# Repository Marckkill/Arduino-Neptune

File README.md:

# Arduino Neptune

> Repositorio do kit Arduino Neptune, um kit didatico para uso em sala de aula. 
> Usado no aprendizado de microcontroladores

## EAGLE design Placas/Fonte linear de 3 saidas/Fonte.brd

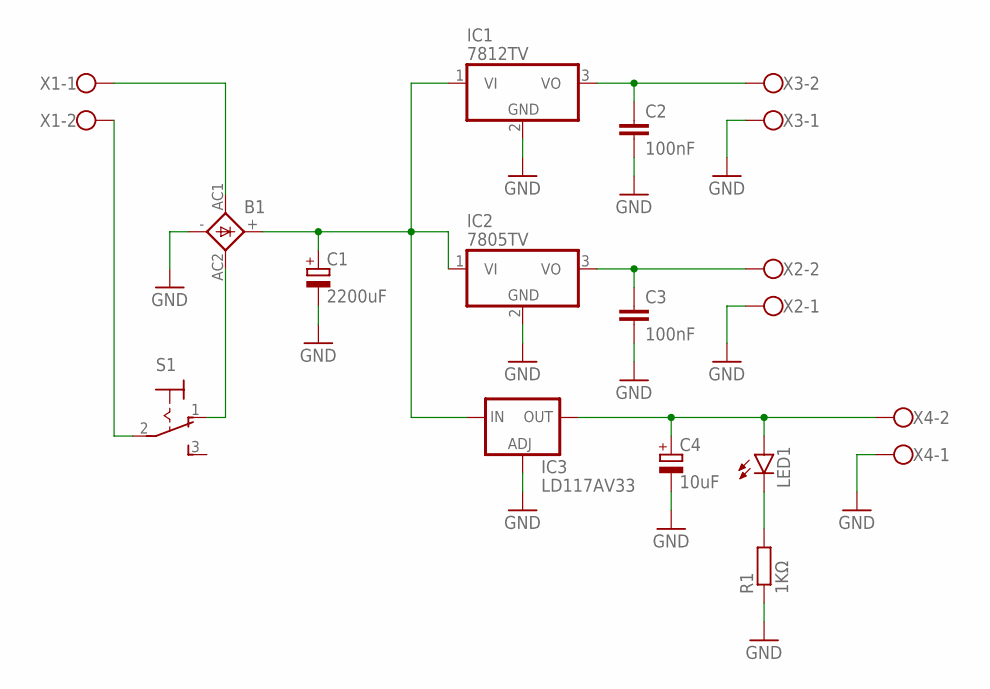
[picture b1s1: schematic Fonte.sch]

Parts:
B1: 2KBB
C1: 2200uF; E5-13
C2, C3: 100nF; C025-024X044
C4: 10uF; E1,8-4
IC1: 7812TV; TO220V
IC2: 7805TV; TO220V
IC3: LD117AV33; TO220S
LED1: LED5MM
R1: 1KΩ; 0207/10
S1: M9040P
X1, X2, X3, X4: W237-102

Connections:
3.3V: C4.+, IC3.2 (OUT), LED1.A, X4.2
5V: C2.1, IC1.3 (VO), X3.2
12V: C3.1, IC2.3 (VO), X2.2
AC1: B1.AC1, X1.1
AC2: S1.2, X1.2
CHAVE: B1.AC2, S1.1 (O)
GND: B1.-, C1.-, C2.2, C3.2, C4.-, IC1.2 (GND), IC2.2 (GND), IC3.1 (ADJ), R1.1, X2.1, X3.1, X4.1
LED: LED1.K (C), R1.2
MAIN: B1.+, C1.+, IC1.1 (VI), IC2.1 (VI), IC3.3 (IN)

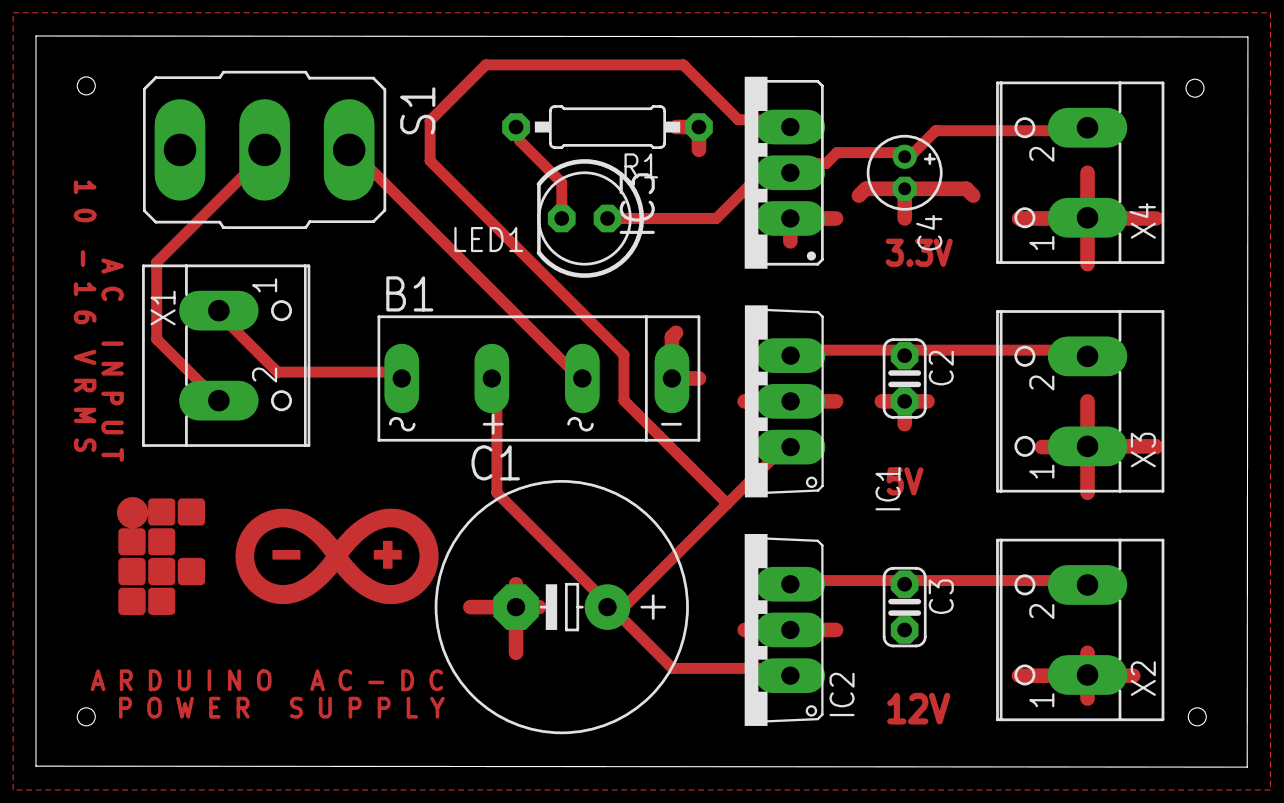
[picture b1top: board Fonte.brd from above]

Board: 2 copper layers, 67.3 x 40.6 mm, 15 parts (0 on the bottom side), 9 nets.

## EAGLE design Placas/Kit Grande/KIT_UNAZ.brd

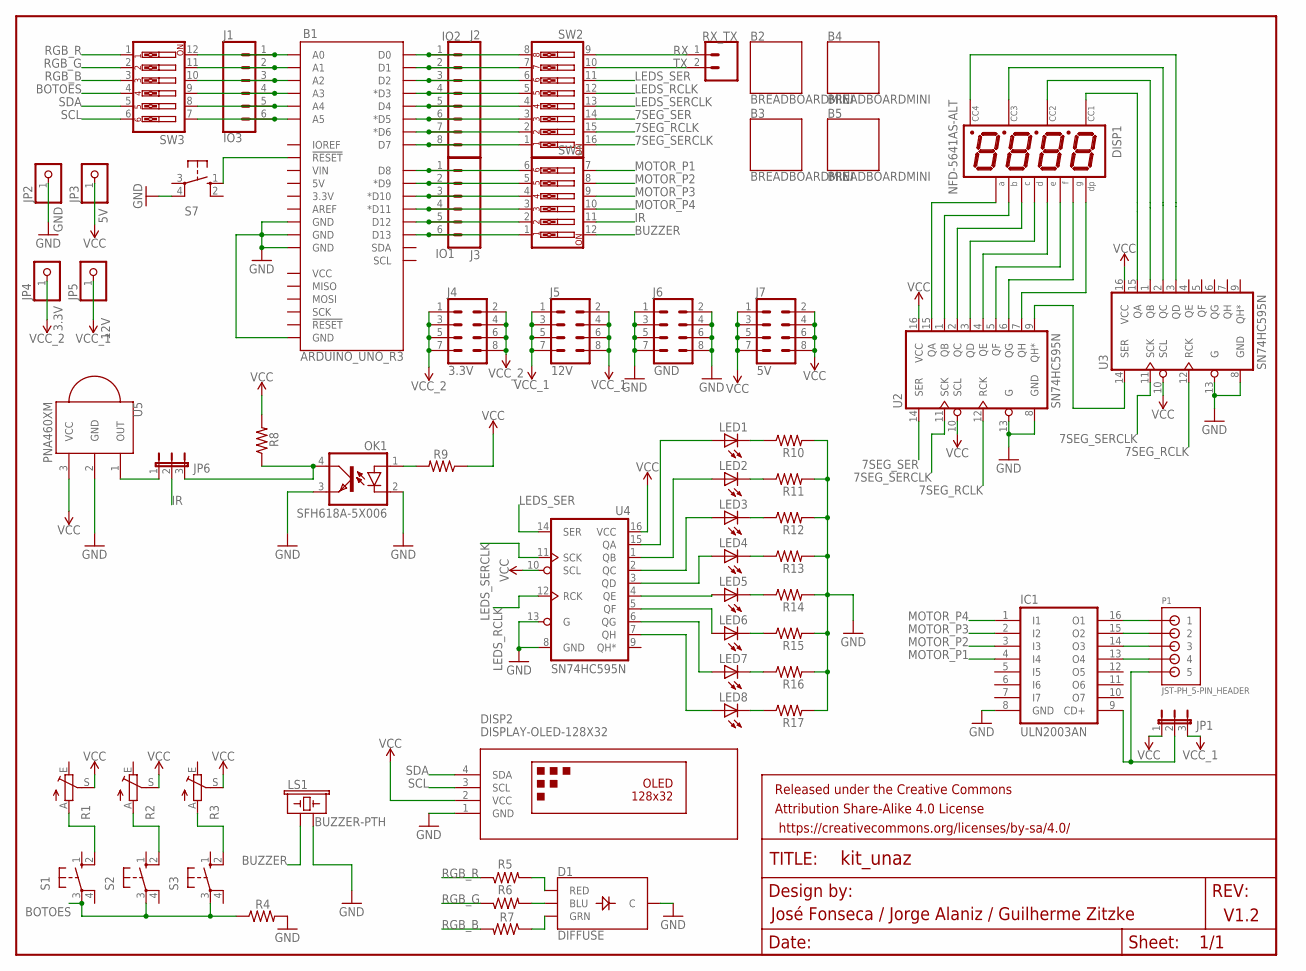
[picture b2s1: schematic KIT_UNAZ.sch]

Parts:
B1: ARDUINO_UNO_R3; ARDUINO_R3
B2, B3, B4, B5: BREADBOARDMINI; BREADBOARD-MINI
D1: DIFFUSE; WS2812B-PTH-KIT
DISP1: NFD-5641AS-ALT; NFD-5641
DISP2: DISPLAY-OLED-128X32
FRAME1: FRAME-LETTER; CREATIVE_COMMONS
IC1: ULN2003AN; DIL16
J1: IO3; 1X06
J2: IO2; 1X08
J3: IO1; 1X06
J4: 3.3V; 2X4
J5: 12V; 2X4
J6: GND; 2X4
J7: 5V; 2X4
JP1, JP6: JP2E; JP2
JP2: GND; 1X01
JP3: 5V; 1X01
JP4: 3.3V; 1X01
JP5: 12V; 1X01
LED1, LED2, LED3, LED4, LED5, LED6, LED7, LED8: LED5MM
LS1: BUZZER-PTH; BUZZER-12MM
OK1: SFH618A-5X006; DIP4-400
P1: JST-PH_5-PIN_HEADER; JST_B5B-PH_HEADER
R1, R2, R3: TRIM_EU-B64Y; B64Y
R4, R5, R6, R7, R8, R9, R10, R11, R12, R13, R14, R15, R16, R17: R-US_0204/7; 0204/7
RX_TX: CONN_02; 1X02
S1, S2, S3, S7: 40-XX; B3F-40XX
SW1, SW3: SW_DIP-6; EDG-06
SW2: SW_DIP-8; EDG-08
U2, U3, U4: SN74HC595N; DIP16
U5: PNA460XM

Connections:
7SEG_RCLK: SW2.15, U2.12 (RCK), U3.12 (RCK)
7SEG_SER: SW2.14, U2.14 (SER)
7SEG_SERCLK: SW2.16, U2.11 (SCK), U3.11 (SCK)
BOTOES: R4.1, S1.3, S2.3, S3.3, SW3.4
BUZZER: LS1.+ (1), SW1.12
GND: B1.GND@1 (GND), B1.GND@2 (GND), B1.GND@3 (GND), B1.GND@4 (GND), D1.2 (C), DISP2.1 (GND), IC1.8 (GND), J6.1, J6.2, J6.3, J6.4, J6.5, J6.6, J6.7, J6.8, JP2.1, LS1.- (2), OK1.2 (C), OK1.3 (EMIT), R4.2, R10.2, R11.2, R12.2, R13.2, R14.2, R15.2, R16.2, R17.2, S7.4 (P1), U2.8 (GND), U2.13 (G), U3.8 (GND), U3.13 (G), U4.8 (GND), U4.13 (G), U5.2 (GND)
IR: JP6.2, SW1.11
LEDS_RCLK: SW2.12, U4.12 (RCK)
LEDS_SER: SW2.11, U4.14 (SER)
LEDS_SERCLK: SW2.13, U4.11 (SCK)
MOTOR_P1: IC1.4 (I4), SW1.7
MOTOR_P2: IC1.3 (I3), SW1.8
MOTOR_P3: IC1.2 (I2), SW1.9
MOTOR_P4: IC1.1 (I1), SW1.10
unnamed: R1.A, S1.2 (S1)
unnamed: R2.A, S2.2 (S1)
unnamed: R3.A, S3.2 (S1)
unnamed: B1.A0, J1.1, SW3.12
unnamed: B1.A1, J1.2, SW3.11
unnamed: B1.A2, J1.3, SW3.10
unnamed: B1.A3, J1.4, SW3.9
unnamed: B1.A4, J1.5, SW3.8
unnamed: B1.A5, J1.6, SW3.7
unnamed: D1.1 (RED), R5.2
unnamed: D1.4 (BLU), R6.2
unnamed: D1.3 (GRN), R7.1
unnamed: DISP1.P$11, U2.15 (QA)
unnamed: B1.D13, J3.6, SW1.1
unnamed: B1.D12, J3.5, SW1.2
unnamed: LED5.K (C), R14.1
unnamed: LED4.K (C), R13.1
unnamed: LED1.K (C), R10.1
unnamed: LED2.K (C), R11.1
unnamed: LED3.K (C), R12.1
unnamed: LED6.K (C), R15.1
unnamed: LED1.A, U4.15 (QA)
unnamed: LED2.A, U4.1 (QB)
unnamed: LED3.A, U4.2 (QC)
unnamed: LED4.A, U4.3 (QD)
unnamed: LED5.A, U4.4 (QE)
unnamed: LED6.A, U4.5 (QF)
unnamed: DISP1.P$7, U2.1 (QB)
unnamed: DISP1.P$4, U2.2 (QC)
unnamed: DISP1.P$2, U2.3 (QD)
unnamed: DISP1.P$1, U2.4 (QE)
unnamed: DISP1.P$10, U2.5 (QF)
unnamed: DISP1.P$5, U2.6 (QG)
unnamed: DISP1.P$3, U2.7 (QH)
unnamed: U2.9 (QH*), U3.14 (SER)
unnamed: LED7.A, U4.6 (QG)
unnamed: LED8.A, U4.7 (QH)
unnamed: B1.D11 (*D11), J3.4, SW1.3
unnamed: B1.D10 (*D10), J3.3, SW1.4
unnamed: B1.D9 (*D9), J3.2, SW1.5
unnamed: DISP1.P$12, U3.15 (QA)
unnamed: B1.RESET@1 (!RESET!), S7.1 (S)
unnamed: DISP1.P$9, U3.1 (QB)
unnamed: DISP1.P$8, U3.2 (QC)
unnamed: DISP1.P$6, U3.3 (QD)
unnamed: IC1.16 (O1), P1.P1 (1)
unnamed: IC1.15 (O2), P1.P2 (2)
unnamed: IC1.14 (O3), P1.P3 (3)
unnamed: IC1.13 (O4), P1.P4 (4)
unnamed: IC1.9 (CD+), JP1.2, P1.P5 (5)
unnamed: JP6.1, U5.1 (OUT)
unnamed: JP6.3, OK1.4 (COL), R8.1
unnamed: OK1.1 (A), R9.2
unnamed: LED7.K (C), R16.1
unnamed: LED8.K (C), R17.1
unnamed: B1.D0, J2.1, SW2.8
unnamed: B1.D1, J2.2, SW2.7
unnamed: B1.D2, J2.3, SW2.6
unnamed: B1.D3 (*D3), J2.4, SW2.5
unnamed: B1.D4, J2.5, SW2.4
unnamed: B1.D5 (*D5), J2.6, SW2.3
unnamed: B1.D6 (*D6), J2.7, SW2.2
unnamed: B1.D8, J3.1, SW1.6
unnamed: B1.D7, J2.8, SW2.1
RGB_B: R7.2, SW3.2
RGB_G: R6.1, SW3.3
RGB_R: R5.1, SW3.1
RX: RX_TX.1, SW2.9
SCL: DISP2.3 (SCL), SW3.6
SDA: DISP2.4 (SDA), SW3.5
TX: RX_TX.2, SW2.10
VCC: DISP2.2 (VCC), J7.1, J7.2, J7.3, J7.4, J7.5, J7.6, J7.7, J7.8, JP1.1, JP3.1, R1.S, R2.S, R3.S, R8.2, R9.1, U2.10 (SCL), U2.16 (VCC), U3.10 (SCL), U3.16 (VCC), U4.10 (SCL), U4.16 (VCC), U5.3 (VCC)
VCC_1: J5.1, J5.2, J5.3, J5.4, J5.5, J5.6, J5.7, J5.8, JP1.3, JP5.1
VCC_2: J4.1, J4.2, J4.3, J4.4, J4.5, J4.6, J4.7, J4.8, JP4.1

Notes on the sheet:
V1.2
José Fonseca / Jorge Alaniz / Guilherme Zitzke

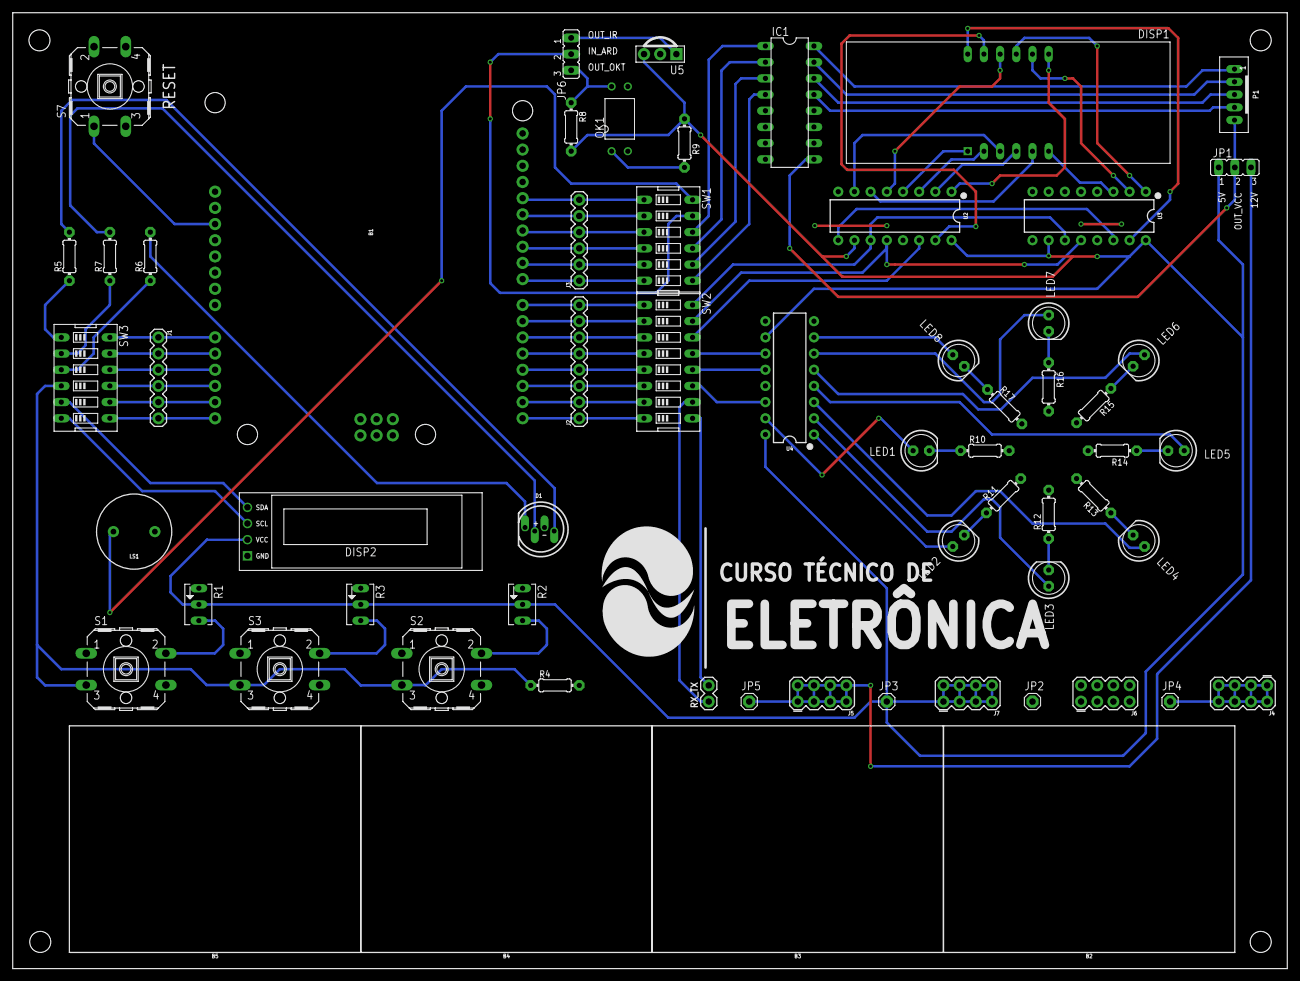
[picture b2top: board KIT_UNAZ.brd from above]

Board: 2 copper layers, 200.0 x 150.0 mm, 63 parts (0 on the bottom side), 88 nets.

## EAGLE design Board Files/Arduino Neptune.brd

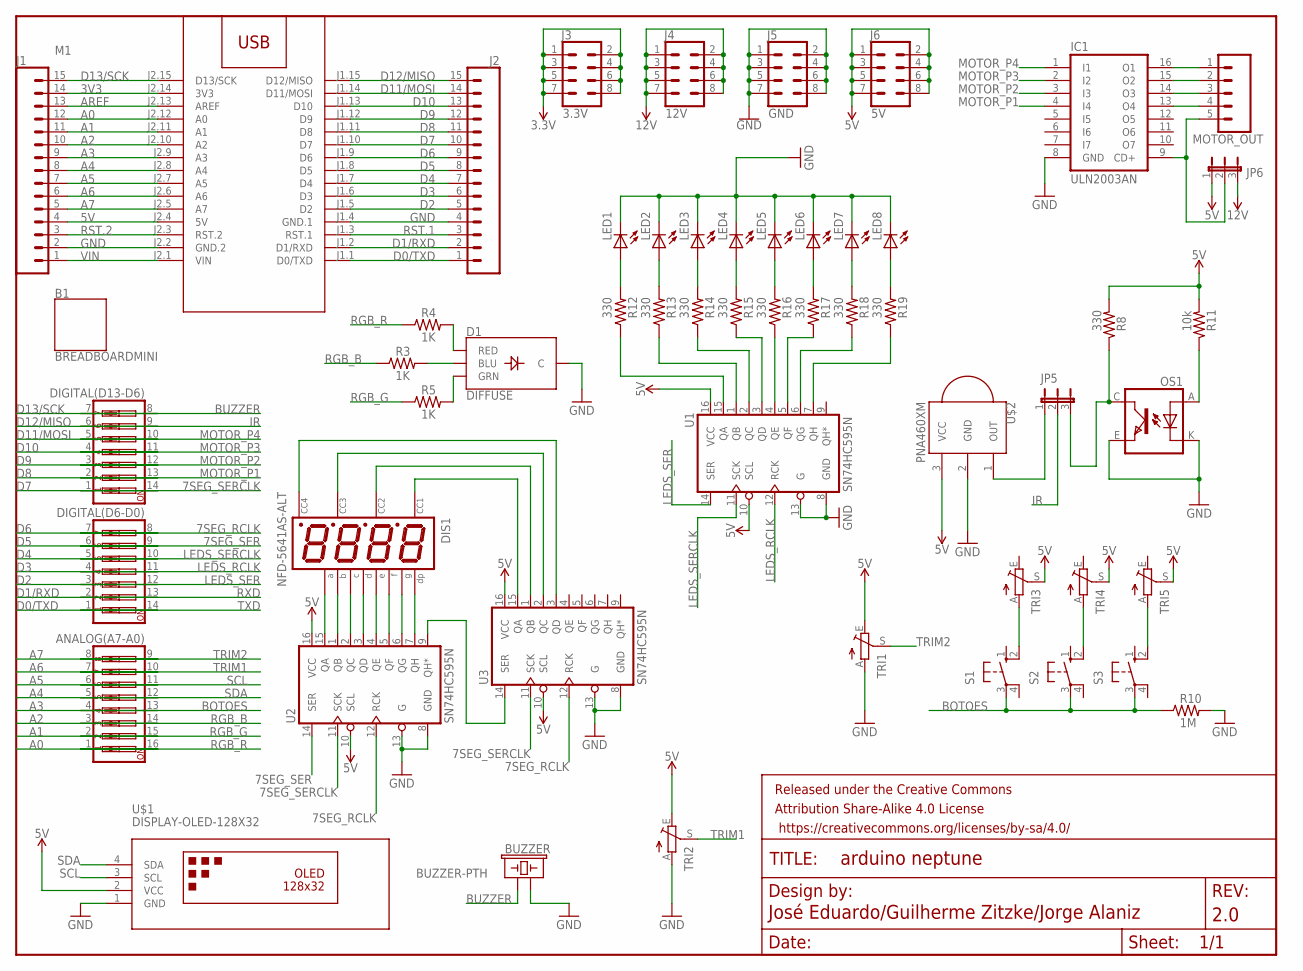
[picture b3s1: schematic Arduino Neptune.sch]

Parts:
ANALOG(A7-A0): SW_DIP-8; EDG-08
B1: BREADBOARDMINI; BREADBOARD-MINI
BUZZER: BUZZER-PTH; BUZZER-12MM
D1: DIFFUSE; LED-RGB-THRU
DIGITAL(D6-D0), DIGITAL(D13-D6): SW_DIP-7; EDG-07
DIS1: NFD-5641AS-ALT; NFD-5641
FRAME2: FRAME-LETTER; CREATIVE_COMMONS
IC1: ULN2003AN; DIL16
J1, J2: CONN_15LOCK_LONGPADS; 1X15_LOCK_LONGPADS
J3: 3.3V; 2X4
J4: 12V; 2X4
J5: GND; 2X4
J6: 5V; 2X4
JP5, JP6: JP2E; JP2
LED1, LED2, LED3, LED4, LED5, LED6, LED7, LED8: LED5MM
M1: ARDUINO-NANO-3.0
MOTOR_OUT: CONN_05JST-VERT; JST-5-PTH-VERT
OS1: TCRT5000
R3, R4, R5: 1K; 0204/7
R8, R12, R13, R14, R15, R16, R17, R18, R19: 330; 0204/7
R10: 1M; 0204/7
R11: 10k; 0204/7
S1, S2, S3: 40-XX; B3F-40XX
TRI1, TRI2, TRI3, TRI4, TRI5: TRIM_EU-B64Y; B64Y
U1, U2, U3: SN74HC595N; DIP16
U$1: DISPLAY-OLED-128X32
U$2: PNA460XM

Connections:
3.3V: J3.1, J3.2, J3.3, J3.4, J3.5, J3.6, J3.7, J3.8
3V3: J1.14, M1.J2.14 (3V3)
5V: J1.4, J6.1, J6.2, J6.3, J6.4, J6.5, J6.6, J6.7, J6.8, JP6.1, M1.J2.4 (5V), R8.2, R11.2, TRI1.E, TRI2.E, TRI3.S, TRI4.S, TRI5.S, U1.10 (SCL), U1.16 (VCC), U2.10 (SCL), U2.16 (VCC), U3.10 (SCL), U3.16 (VCC), U$1.2 (VCC), U$2.3 (VCC)
7SEG_RCLK: DIGITAL(D6-D0).7, U2.12 (RCK), U3.12 (RCK)
7SEG_SER: DIGITAL(D6-D0).6, U2.14 (SER)
7SEG_SERCLK: DIGITAL(D13-D6).1, U2.11 (SCK), U3.11 (SCK)
12V: J4.1, J4.2, J4.3, J4.4, J4.5, J4.6, J4.7, J4.8, JP6.3
A0: ANALOG(A7-A0).16, J1.12, M1.J2.12 (A0)
A1: ANALOG(A7-A0).15, J1.11, M1.J2.11 (A1)
A2: ANALOG(A7-A0).14, J1.10, M1.J2.10 (A2)
A3: ANALOG(A7-A0).13, J1.9, M1.J2.9 (A3)
A4: ANALOG(A7-A0).12, J1.8, M1.J2.8 (A4)
A5: ANALOG(A7-A0).11, J1.7, M1.J2.7 (A5)
A6: ANALOG(A7-A0).10, J1.6, M1.J2.6 (A6)
A7: ANALOG(A7-A0).9, J1.5, M1.J2.5 (A7)
AREF: J1.13, M1.J2.13 (AREF)
BOTOES: ANALOG(A7-A0).4, R10.1, S1.3, S2.3, S3.3
BUZZER: BUZZER.+ (1), DIGITAL(D13-D6).7
D0/TXD: DIGITAL(D6-D0).14, J2.1, M1.J1.1 (D0/TXD)
D1/RXD: DIGITAL(D6-D0).13, J2.2, M1.J1.2 (D1/RXD)
D2: DIGITAL(D6-D0).12, J2.5, M1.J1.5 (D2)
D3: DIGITAL(D6-D0).11, J2.6, M1.J1.6 (D3)
D4: DIGITAL(D6-D0).10, J2.7, M1.J1.7 (D4)
D5: DIGITAL(D6-D0).9, J2.8, M1.J1.8 (D5)
D6: DIGITAL(D6-D0).8, J2.9, M1.J1.9 (D6)
D7: DIGITAL(D13-D6).14, J2.10, M1.J1.10 (D7)
D8: DIGITAL(D13-D6).13, J2.11, M1.J1.11 (D8)
D9: DIGITAL(D13-D6).12, J2.12, M1.J1.12 (D9)
D10: DIGITAL(D13-D6).11, J2.13, M1.J1.13 (D10)
D11/MOSI: DIGITAL(D13-D6).10, J2.14, M1.J1.14 (D11/MOSI)
D12/MISO: DIGITAL(D13-D6).9, J2.15, M1.J1.15 (D12/MISO)
D13/SCK: DIGITAL(D13-D6).8, J1.15, M1.J2.15 (D13/SCK)
GND: BUZZER.- (2), D1.2 (C), IC1.8 (GND), J1.2, J2.4, J5.1, J5.2, J5.3, J5.4, J5.5, J5.6, J5.7, J5.8, LED1.K (C), LED2.K (C), LED3.K (C), LED4.K (C), LED5.K (C), LED6.K (C), LED7.K (C), LED8.K (C), M1.J1.4 (GND.1), M1.J2.2 (GND.2), OS1.E (EMITTER), OS1.K (CATHODE), R10.2, TRI1.A, TRI2.A, U1.8 (GND), U1.13 (G), U2.8 (GND), U2.13 (G), U3.8 (GND), U3.13 (G), U$1.1 (GND), U$2.2 (GND)
IR: DIGITAL(D13-D6).6, JP5.2
LEDS_RCLK: DIGITAL(D6-D0).4, U1.12 (RCK)
LEDS_SER: DIGITAL(D6-D0).3, U1.14 (SER)
LEDS_SERCLK: DIGITAL(D6-D0).5, U1.11 (SCK)
MOTOR_P1: DIGITAL(D13-D6).2, IC1.4 (I4)
MOTOR_P2: DIGITAL(D13-D6).3, IC1.3 (I3)
MOTOR_P3: DIGITAL(D13-D6).4, IC1.2 (I2)
MOTOR_P4: DIGITAL(D13-D6).5, IC1.1 (I1)
unnamed: D1.3 (GRN), R5.2
unnamed: D1.4 (BLU), R3.2
unnamed: D1.1 (RED), R4.2
unnamed: IC1.16 (O1), MOTOR_OUT.1
unnamed: IC1.9 (CD+), JP6.2, MOTOR_OUT.5
unnamed: LED8.A, R19.2
unnamed: LED7.A, R18.2
unnamed: LED6.A, R17.2
unnamed: R16.1, U1.4 (QE)
unnamed: LED5.A, R16.2
unnamed: LED4.A, R15.2
unnamed: LED3.A, R14.2
unnamed: LED2.A, R13.2
unnamed: LED1.A, R12.2
unnamed: JP5.1, U$2.1 (OUT)
unnamed: OS1.A (ANODE), R11.1
unnamed: JP5.3, OS1.C (COLLECTOR), R8.1
unnamed: IC1.15 (O2), MOTOR_OUT.2
unnamed: IC1.14 (O3), MOTOR_OUT.3
unnamed: IC1.13 (O4), MOTOR_OUT.4
unnamed: DIS1.P$11, U2.15 (QA)
unnamed: DIS1.P$7, U2.1 (QB)
unnamed: DIS1.P$4, U2.2 (QC)
unnamed: DIS1.P$2, U2.3 (QD)
unnamed: DIS1.P$1, U2.4 (QE)
unnamed: DIS1.P$10, U2.5 (QF)
unnamed: DIS1.P$5, U2.6 (QG)
unnamed: DIS1.P$3, U2.7 (QH)
unnamed: U2.9 (QH*), U3.14 (SER)
unnamed: DIS1.P$8, U3.2 (QC)
unnamed: DIS1.P$9, U3.1 (QB)
unnamed: DIS1.P$12, U3.15 (QA)
unnamed: DIS1.P$6, U3.3 (QD)
unnamed: R12.1, U1.15 (QA)
unnamed: R13.1, U1.1 (QB)
unnamed: R14.1, U1.2 (QC)
unnamed: R15.1, U1.3 (QD)
unnamed: R17.1, U1.5 (QF)
unnamed: R18.1, U1.6 (QG)
unnamed: S1.2 (S1), TRI3.A
unnamed: R19.1, U1.7 (QH)
unnamed: S2.2 (S1), TRI4.A
unnamed: S3.2 (S1), TRI5.A
RGB_B: ANALOG(A7-A0).3, R3.1
RGB_G: ANALOG(A7-A0).2, R5.1
RGB_R: ANALOG(A7-A0).1, R4.1
RST.1: J2.3, M1.J1.3 (RST.1)
RST.2: J1.3, M1.J2.3 (RST.2)
RXD: DIGITAL(D6-D0).2
SCL: ANALOG(A7-A0).6, U$1.3 (SCL)
SDA: ANALOG(A7-A0).5, U$1.4 (SDA)
TRIM1: ANALOG(A7-A0).7, TRI2.S
TRIM2: ANALOG(A7-A0).8, TRI1.S
TXD: DIGITAL(D6-D0).1
VIN: J1.1, M1.J2.1 (VIN)

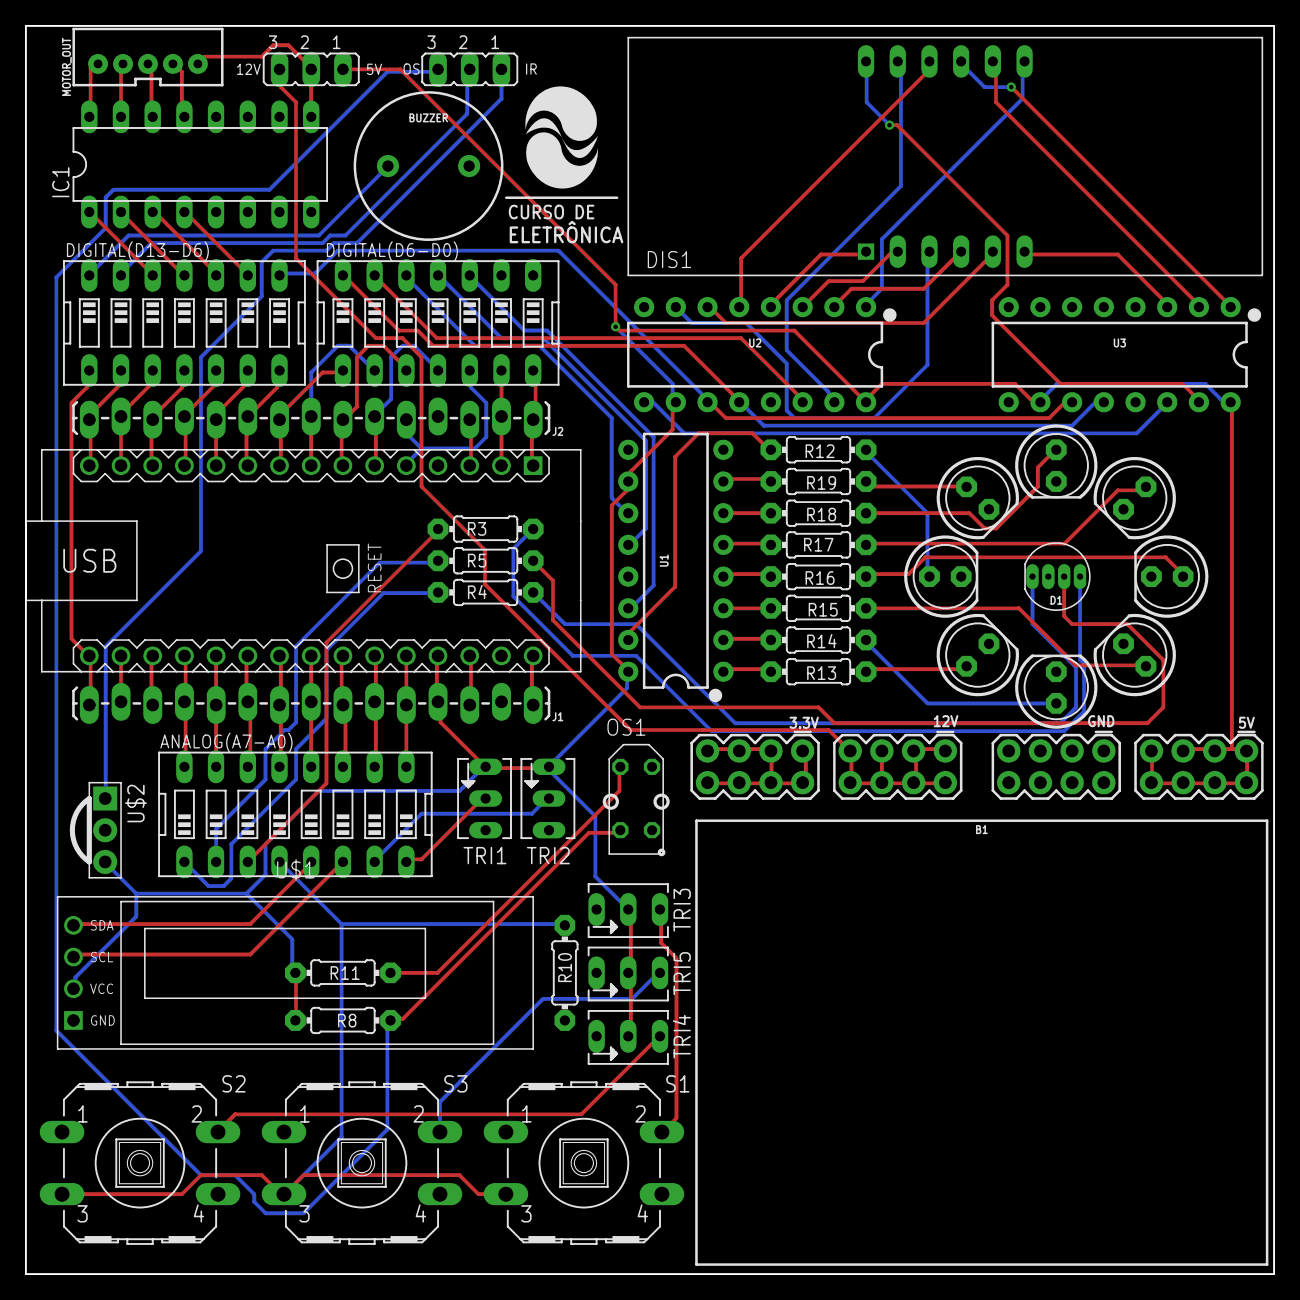
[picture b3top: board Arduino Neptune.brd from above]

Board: 2 copper layers, 100.0 x 100.0 mm, 55 parts (0 on the bottom side), 94 nets.

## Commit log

2022-08-16 Fotos novas
2022-08-30 Clean up

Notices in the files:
parts and their libraries:
diy-modules: Released under the Creative Commons Attribution 4.0 International License: http://creativecommons.org/licenses/by/4.0
SparkFun-Aesthetics: Licensing: Creative Commons ShareAlike 4.0 International - https://creativecommons.org/licenses/by-sa/4.0
